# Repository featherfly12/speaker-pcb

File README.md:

# Speaker PCB

In this github, there is a pcb design that has a total of 1 song!  

| Part | What it is | What it does in this circuit |
|------|-----------|------------------------------|
| STM32L433CCT6 | Microcontroller | Runs your code — reads the song from flash memory and streams it to the speaker amplifier over I2S |
| W25Q128JVEIQ | 16 MB flash memory chip | Stores the raw audio file (like a tiny solid-state drive) so the microcontroller can play it back |
| MAX98357AETE+T | I2S audio amplifier | Takes the digital audio stream from the microcontroller and amplifies it directly via pulse-width modulation (PWM) — rapid switching whose pulse widths track the signal, which the speaker smooths back into sound. This switching design is what makes it a class-D amplifier, and what lets it drive a speaker efficiently from such a small chip. |
| AP2112K-3.3TRG1 | 3.3V Low-dropout Regulator (LDO) | Steps down the input voltage to the stable 3.3V that the microcontroller and other chips need to operate safely. This can eliminate most noise from the power supply, making the 3.3V "clean" power. |
| SMAJ13A | TVS (transient voltage suppression) diode | Prevents voltage spikes on the power input. |
| PESD3V3L4UG,115 | 4-channel ESD protection array | Guards four signal lines at once against static electricity (ESD). Static can silently kill chips when you touch their pins!  |
| PESD3V3L1BA | Single-channel ESD protection diode | Same idea as above, but for one signal line.|
|ECS-80-12-33-JGN-TR | 8MHz Crystal | A crystal that oscillates within 20 ppm of 8MHz when driven by the MCU (with some helper capacitors). This makes the clock of the MCU much more precise, and prevents the frequency of the song from drifting while it is playing. |

## Programming the Board
Music from an MP3 file is converted into pure binary 16-bit data at 31.25kHz using scripts in `firmware/media`. The output, `media.bin`, may be flashed onto the chip using an external loader and [STM32CubeProgrammer](https://www.st.com/en/development-tools/stm32cubeprog.html). The external loader for this custom PCB was written in the folder `firmware/W25Q128_HAL`, and the actual compiled loader file is  `W25Q128_STM32L433_HAL.stldr`. Once the external memory is programmed with the song, the STM32 itself can be flashed with the `music_player` project using [STM32CubeIDE](https://www.st.com/en/development-tools/stm32cubeide.html). 

These programs were written with the help of Claude Code / Sonnet 4.6.

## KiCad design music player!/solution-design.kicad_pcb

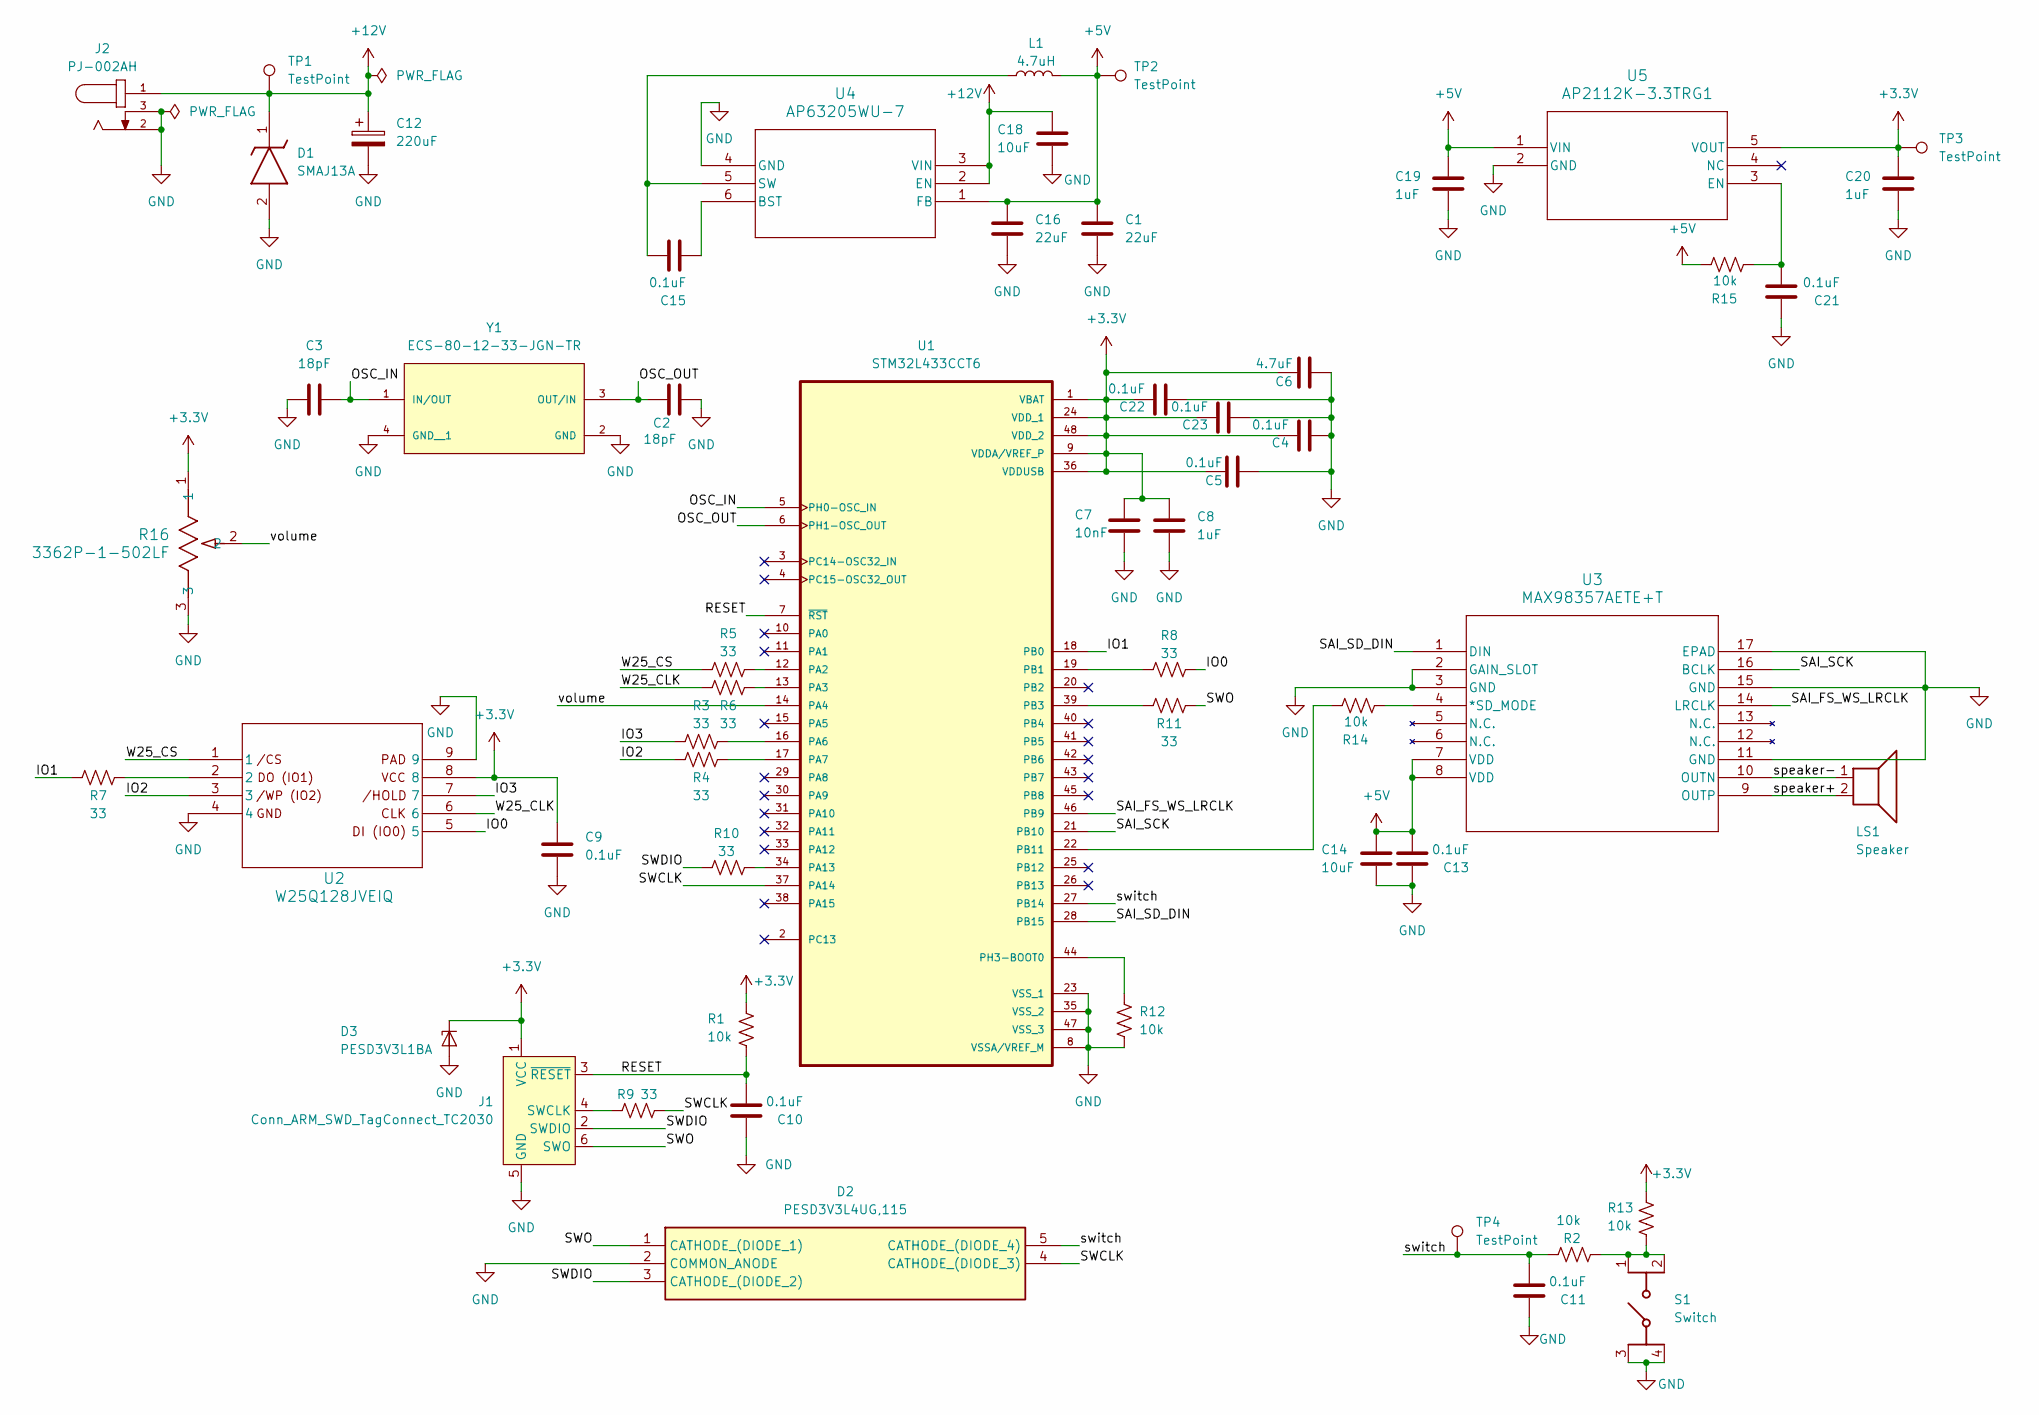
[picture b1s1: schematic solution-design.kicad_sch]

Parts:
C1, C16: 22uF; C_1206_3216Metric_Pad1.33x1.80mm_HandSolder; JLC Part # C12891
C2, C3: 18pF; C_0402_1005Metric_Pad0.74x0.62mm_HandSolder; JLC Part # C1549
C4, C5, C9, C10, C11, C13, C15, C21, C22, C23: 0.1uF; C_0603_1608Metric_Pad1.08x0.95mm_HandSolder; JLC Part # C14663
C6: 4.7uF; C_1206_3216Metric_Pad1.33x1.80mm_HandSolder; JLC Part # C29823
C7: 10nF; C_0805_2012Metric_Pad1.18x1.45mm_HandSolder; JLC Part # C1710
C8, C19, C20: 1uF; C_0603_1608Metric_Pad1.08x0.95mm_HandSolder; JLC Part # C15849
C12: 220uF; CP_Radial_D10.0mm_P5.00mm
C14, C18: 10uF; C_1206_3216Metric_Pad1.33x1.80mm_HandSolder; JLC Part # C13585
D1: SMAJ13A; DIONM5126X250N; Mouser Part Number 576-SMAJ13A
D2: PESD3V3L4UG,115; PESD3V3L4UG115; Mouser Part Number 771-PESD3V3L4UG-T/R
D3: PESD3V3L1BA; D_SOD-323_HandSoldering; MFG # PESD3V3L1BA; JLC Part # C2687129
J1: Conn_ARM_SWD_TagConnect_TC2030; Tag-Connect_TC2030-IDC-FP_2x03_P1.27mm_Vertical
J2: PJ-002AH; CUI_PJ-002AH
L1: 4.7uH; IND_NRS6028T0R9NMGJV_TAY; MFG # NRS6028T4R7MMGKV
LS1: Speaker; CES-46257-24-L200
R1, R2, R12, R13, R14, R15: 10k; R_1206_3216Metric_Pad1.30x1.75mm_HandSolder; JLC Part # C17902
R3, R4, R5, R6, R7, R8, R9, R10, R11: 33; R_0603_1608Metric_Pad0.98x0.95mm_HandSolder; JLC # C23140
R16: 3362P-1-502LF; POT_3362P
S1: Switch; PTS647SK70SMTR2LFS; MFG # PTS647SM70SMTR2 LFS
TP1, TP2, TP3: TestPoint; TestPoint_Loop_D2.54mm_Drill1.5mm_Beaded
TP4: TestPoint; TestPoint_Loop_D1.80mm_Drill1.0mm_Beaded
U1: STM32L433CCT6; QFP50P900X900X160-48N; MFG # STM32L433CCT6; JLC Part # C110061
U2: W25Q128JVEIQ; WSON_128JVEIQ_WIN-M; MFG # W25Q128JVEIQ; JLC Part # C2456297
U3: MAX98357AETE+T; 21-0136I_T1633-4_MXM-M; MFG # MAX98357AETE+T; JLC Part # C910544
U4: AP63205WU-7; SOIC_05WU-7_DIO-M
U5: AP2112K-3.3TRG1; SOT_RG1_DIO-M
Y1: ECS-80-12-33-JGN-TR; XTAL_ECS-240-8-33-AGN-TR

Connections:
+3.3V: C4.1, C5.1, C6.1, C7.1, C8.1, C9.2, C20.1, C22.1, C23.1, D3.1 (K1), J1.1 (VCC), R1.1, R13.2, R16.1, TP3.1 (1_1), U1.1 (VBAT), U1.9 (VDDA/VREF_P), U1.24 (VDD_1), U1.36 (VDDUSB), U1.48 (VDD_2), U2.8, U5.5 (VOUT)
+5V: C1.1, C13.1, C14.1, C16.1, C19.1, L1.2, R15.1, TP2.1 (1_1), U3.7 (VDD), U3.8 (VDD), U4.1 (FB), U5.1 (VIN)
+12V: C12.1, C18.1, D1.1 (K), J2.1, TP1.1 (1_1), U4.2 (EN), U4.3 (VIN)
/IO0: R8.2, U2.5
/IO1: R7.1, U1.18 (PB0)
/IO2: R4.1, U2.3
/IO3: R3.1, U2.7
/OSC_IN: C3.2, U1.5 (PH0-OSC_IN), Y1.1 (IN/OUT)
/OSC_OUT: C2.2, U1.6 (PH1-OSC_OUT), Y1.3 (OUT/IN)
/RESET: C10.1, J1.3 (~RESET), R1.2, U1.7 (~RST)
/SAI_FS_WS_LRCLK: U1.46 (PB9), U3.14 (LRCLK)
/SAI_SCK: U1.21 (PB10), U3.16 (BCLK)
/SAI_SD_DIN: U1.28 (PB15), U3.1 (DIN)
/SWCLK: D2.4 (CATHODE_(DIODE_3)), R9.2, U1.37 (PA14)
/SWDIO: D2.3 (CATHODE_(DIODE_2)), J1.2 (SWDIO), R10.1
/SWO: D2.1 (CATHODE_(DIODE_1)), J1.6 (SWO), R11.2
/W25_CLK: R6.1, U2.6
/W25_CS: R5.1, U2.1
/speaker+: LS1.2, U3.9 (OUTP)
/speaker-: LS1.1, U3.10 (OUTN)
/switch: C11.1, D2.5 (CATHODE_(DIODE_4)), R2.1, TP4.1 (1_1), U1.27 (PB14)
/volume: R16.2, U1.14 (PA4)
GND: C1.2, C2.1, C3.1, C4.2, C5.2, C6.2, C7.2, C8.2, C9.1, C10.2, C11.2, C12.2, C13.2, C14.2, C16.2, C18.2, C19.2, C20.2, C21.2, C22.2, C23.2, D1.2 (A), D2.2 (COMMON_ANODE), D3.2 (A), J1.5 (GND), J2.2, J2.3, R12.2, R16.3, S1.3 (COM_1), S1.4 (COM_2), U1.8 (VSSA/VREF_M), U1.23 (VSS_1), U1.35 (VSS_2), U1.47 (VSS_3), U2.4, U2.9, U3.2 (GAIN_SLOT), U3.3 (GND), U3.11 (GND), U3.15 (GND), U3.17 (EPAD), U4.4 (GND), U5.2 (GND), Y1.2 (GND), Y1.4 (GND__1)
unnamed: J1.4 (SWCLK), R9.1
unnamed: R7.2, U2.2
unnamed: R2.2, R13.1, S1.1 (NO_1), S1.2 (NO_2)
unnamed: R5.2, U1.12 (PA2)
unnamed: R6.2, U1.13 (PA3)
unnamed: R3.2, U1.16 (PA6)
unnamed: R4.2, U1.17 (PA7)
unnamed: R10.2, U1.34 (PA13)
unnamed: R8.1, U1.19 (PB1)
unnamed: R11.1, U1.39 (PB3)
unnamed: R14.1, U1.22 (PB11)
unnamed: R12.1, U1.44 (PH3-BOOT0)
unnamed: R14.2, U3.4 (*SD_MODE)
unnamed: C15.2, U4.6 (BST)
unnamed: C15.1, L1.1, U4.5 (SW)
unnamed: C21.1, R15.2, U5.3 (EN)

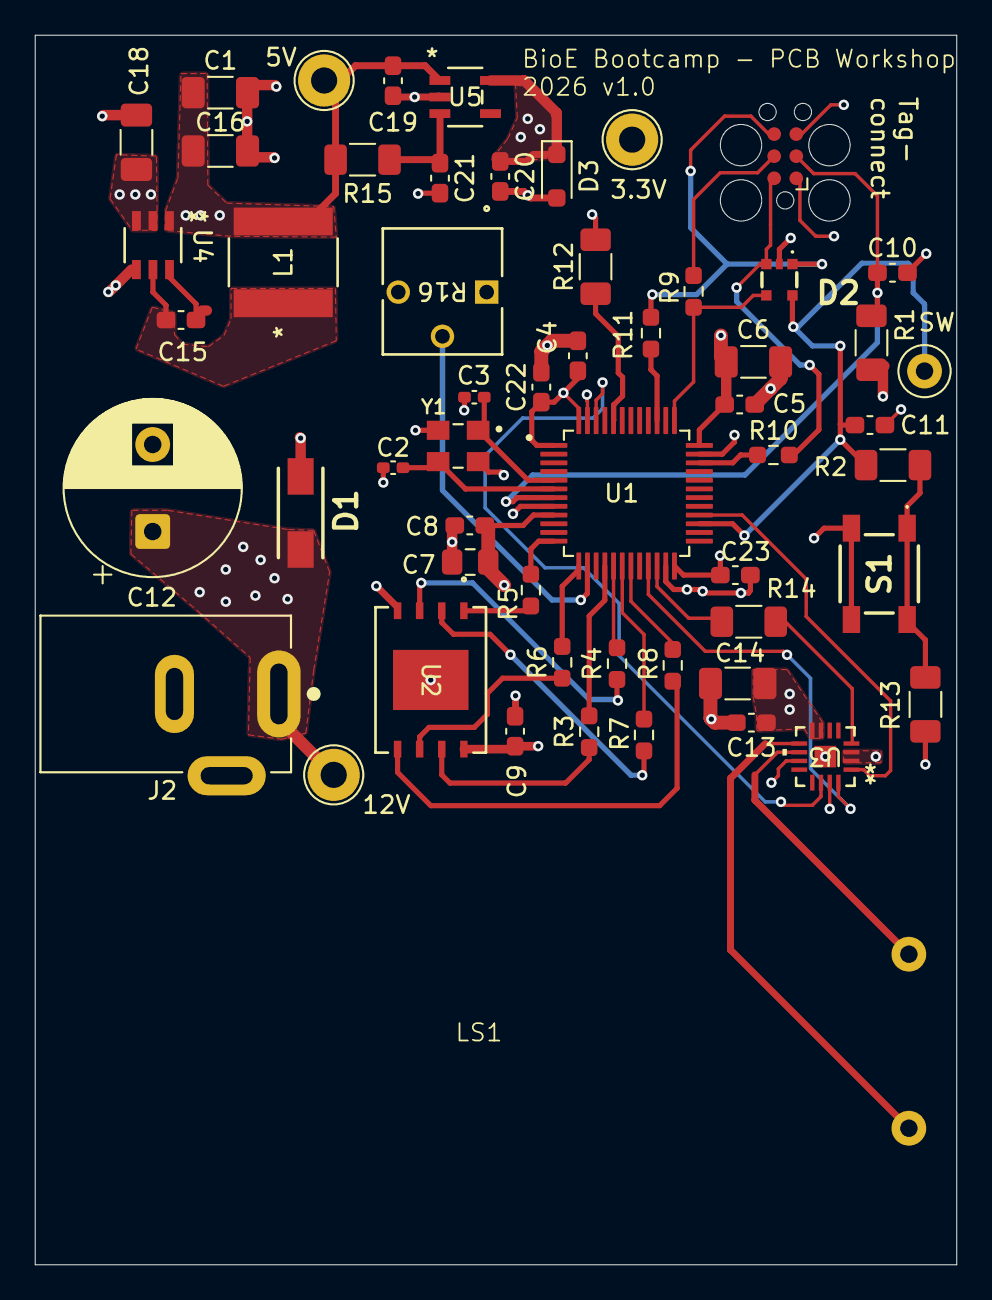
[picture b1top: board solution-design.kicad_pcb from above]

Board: 4 copper layers, 52.9 x 70.7 mm, 56 parts (0 on the bottom side), 39 nets.

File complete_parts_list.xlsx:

Item | MFG # | Mouser Part # | Price | Qnty/PCB | Link | Notes
Integrated Circuits
IC REG BUCK 5V 2A TSOT23-6 | AP63205WU-7 | 621-AP63205WU-7 | 0.58099999999999996 | 15
Linear Voltage Regulator IC Positive Fixed 1 Output 600mA SOT-25 | AP2112K-3.3TRG1 | 621-AP2112K-3.3TRG1 | 0.17599999999999999 | 15
Passives
CAP ALUM 220UF 20% 50V RADIAL TH | ECA-1HM221 | 667-ECA-1HM221B | 0.309 | 15
4.7 µH Semi-Shielded Drum Core, Wirewound Inductor 3 A 40.3mOhm Max Nonstandard | NRS6028T4R7MMGKV | 963-NRS6028T4R7MMGKV | 0.23799999999999999 | 15
TRIMMER 5K OHM 0.5W PC PIN TOP | 3362P-1-502LF | 652-3362P-1-502LF | 0.754 | 15
Misc
CONN PWR JACK 2X5.5MM SOLDER | PJ-002AH | 490-PJ-002AH | 0.54700000000000004 | 15
AC/DC WALL MOUNT ADAPTER 12V 24W | PYA24A120200 | 552-PYA24A120200 | 7.7 | 15
Speaker (4 Ohm) | CES-46257-24-L200 | 179-CES-46257-24L200 | 4.9800000000000004 | 15
CRYSTAL 8.0000MHZ 12PF SMD | ECS-80-12-33-JGN-TR | 520-80-12-33-JGN-TR | 0.50800000000000001 | 15
SWITCH TACTILE SPST-NO 0.05A 12V | PTS647SM70SMTR2 LFS | 611-PTS647SM70SMTR2L | 0.23499999999999999 | 15
Non-disposable Materials
ST-LINK V3 PROG FOR STM32 | STLINK-V3MINIE | 511-STLINK-V3MINIE | 26.47 | 1 |  | Total | 266.89
TC2030-CTX-STDC14 for use with STM32 processors with STLINK-V3/STLINK-V3MINI | TC2030-CTX-ST14 | NA | 43 |  | 6pin Plug-of-Nails Cable for STM32 MCU & STLINK-V3 | Tag-Connect
Double Sided Tape Strong White Foam Tape 1" x 18Ft Made of 3M Heavy Duty Mounti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 | NA | NA | 15.99 |  | Amazon.com: Double Sided Tape Strong White Foam Tape 1/2" x 18Ft Made of 3M Hea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 | For mounting speaker
Anti Static Mat for Pc ESD Mat: 24"X36" Soldering Table Mat Kit Computer Electr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 | NA | NA | 43 |  | Anti Static Mat for Pc ESD Mat: 17"X25" Soldering Table Mat Kit Computer Electr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
Parts ordered with PCBA
Part | Designator | Footprint | JLC Part #
22uF | C1,C16 | Capacitor_SMD:C_1206_3216Metric_Pad1.33x1.80mm_HandSolder | C12891
18pF | C2,C3 | Capacitor_SMD:C_0402_1005Metric_Pad0.74x0.62mm_HandSolder | C1549
0.1uF | C4,C5,C9,C10,C11,C13,C15,C21,C22,C23 | Capacitor_SMD:C_0603_1608Metric_Pad1.08x0.95mm_HandSolder | C14663
4.7uF | C6 | Capacitor_SMD:C_1206_3216Metric_Pad1.33x1.80mm_HandSolder | C29823
10nF | C7 | Capacitor_SMD:C_0805_2012Metric_Pad1.18x1.45mm_HandSolder | C1710
1uF | C8,C19,C20 | Capacitor_SMD:C_0603_1608Metric_Pad1.08x0.95mm_HandSolder | C15849
10uF | C14,C18 | Capacitor_SMD:C_1206_3216Metric_Pad1.33x1.80mm_HandSolder | C13585
SMAJ13A | D1 | project_footprints:DIONM5126X250N | C148214
PESD3V3L4UG,115 | D2 | project_footprints:PESD3V3L4UG115 | C70500
PESD3V3L1BA | D3 | Diode_SMD:D_SOD-323_HandSoldering | C2687129
10k | R1,R2,R12,R13,R14,R15 | Resistor_SMD:R_1206_3216Metric_Pad1.30x1.75mm_HandSolder | C17902
33ohm | R3,R4,R5,R6,R7,R8,R9,R10,R11 | Resistor_SMD:R_0603_1608Metric_Pad0.98x0.95mm_HandSolder | C23140
STM32L433CCT6 | U1 | project_footprints:QFP50P900X900X160-48N | C110061
W25Q128JVEIQ | U2 | project_footprints:WSON_128JVEIQ_WIN-M | C2456297
MAX98357AETE+T | U3 | project_footprints:21-0136I_T1633-4_MXM-M | C910544
